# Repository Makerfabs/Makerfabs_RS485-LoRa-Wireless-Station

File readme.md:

# Industrial-grade Soil Remote Monitor

```c++
/*
Version:		V2.0
Author:			Vincent
Create Date:	2023/3/1
Note:
		2023/3/1	V2.0: Use new sensor, change request code.
*/
```

[toc]

# Makerfabs

[Makerfabs home page](https://www.makerfabs.com/)

[Makerfabs Wiki](https://wiki.makerfabs.com/)

# Industrial-grade Soil Remote Monitor

## Intruduce

Product Link ：[Industrial-grade Soil Remote Monitor(Humidity/ Temperature/ PH/ Nitrogen/ Phosphorus/ Potassium)](https://www.makerfabs.com/industrial-grade-soil-remote-monitor.html) 

Wiki Link : [RS485-LoRa Wireless Station](https://wiki.makerfabs.com/Industrial-grade_Soil_Remote_Monitor.html) 

With the development of agricultural modernization and the popularization of precision agriculture, the remote monitoring of soil parameters such as temperature, moisture, PH, and so on, becomes more important.

This Industry-grade soil remote monitor intends for these applications of agriculture, it is mainly composed of 2 parts:

**1. Remote monitor station with RS485:** developed by Makerfabs, it converts the RS485 signal, which is usually used in agricultural field applications, to wireless connections WIFI (if there is) or Lora, or Bluetooth.
**2. Industrial-grade Soil Sensor:** unlike some other maker-level soil sensors that only output analog voltage that reflects the soil status/changes but not the absolute value, this sensor measures the soil parameters such Temperature/Moisture/PH/Nitrogen/ Phosphorus/Potassium.., with calculated true output, so users can get to know the real soil parameters.

## Feature

- ESP32 WROOM module onboard with the WiFi and Bluetooth
- Arduino Compatible: You can play it with Arduino IDE
- Onboard LoRa module (433Mhz or 868Mhz or 915Mhz)
- 0.91inch I2C OLED display
- Sensor part is waterproof, completely sealed
- Measuring range: -40℃~80℃，0~100% moisture
- Measuring accuracy: ±0.5℃，±3% moisture
- Communication distance: Lora: 2km or more; WIFI: No such parameter
- Power by Micro USB, battery, or DC 5V
- 1000mAh battery, charger IC onboard

# Code

## Compiler Options

**If you have any questions，such as how to install the development board, how to download the code, how to install the library. Please refer to :[Makerfabs_FAQ](https://github.com/Makerfabs/Makerfabs_FAQ)**

- Install board : ESP32 .
- Install library : Adafruit GFX library (V1.10.11) , Adafruit SSD1306 library (V2.4.6) and RadioLib library 4.0.6.
- Upload codes, select "ESP32 Dev Module"

## Sensor User Manual

Cable definition:

- Grey cable: DC 5V power supply +
- Black line: Power ground (GND)
- Yellow and green wires: RS485-A;
- Brown cable: RS485-B.

The sensor uses Modbus RTU.

Request Command：**01 04 00 00 00 07 B1 C8**

- 0x01 Sensor address; 
- 0x04 function code; 
- 0x00 0x00 read register start position; 
- 0x00 0x07 Number of registers read; 
- 0xB1 0xC8  Check

Receive Data：**01 04 0E 01 D7 01 07 00 00 00 46 00 0F 00 14 00 32 CC 93**

- 0x01 Sensor address;
- 0x04 function code;
- 0x0E data length;
- 0x01 0xD7 Soil moisture data 01 D7 (hexadecimal) is 47.1%
- 0x01 0x07 Soil Temperature Data 01 07 (hexadecimal) is 26.3 ° C
- 0x00 0x00 blank
- 0x00 0x46 PH data 00 46 (hexadecimal) is 7.0
- 0x00 0x0F Soil Nitrogen data 00 0F (hexadecimal) is 15mg/kg
- 0x00 0x14 Soil Phosphorus data 00 14 (hexadecimal) is 20mg/kg
- 0x00 0x32 Soil potassium data 00 32 (hexadecimal) is 50mg/kg
- 0xCC 0x93 check

| Parameter   | Address | Range       | Sampling Value | Action    |
| ----------- | ------- | ----------- | -------------- | --------- |
| Humidity    | 0000H   | 0~100%      | /10            | Only Read |
| Temperature | 0001H   | -40~80℃     | /10            | Only Read |
| PH          | 0003H   | 4~9         | /10            | Only Read |
| Nitrogen    | 0004H   | 0~1999mg/kg | /1             | Only Read |
| Phosphorus  | 0005H   | 0~1999mg/kg | /1             | Only Read |
| Potassium   | 0006H   | 0~1999mg/kg | /1             | Only Read |

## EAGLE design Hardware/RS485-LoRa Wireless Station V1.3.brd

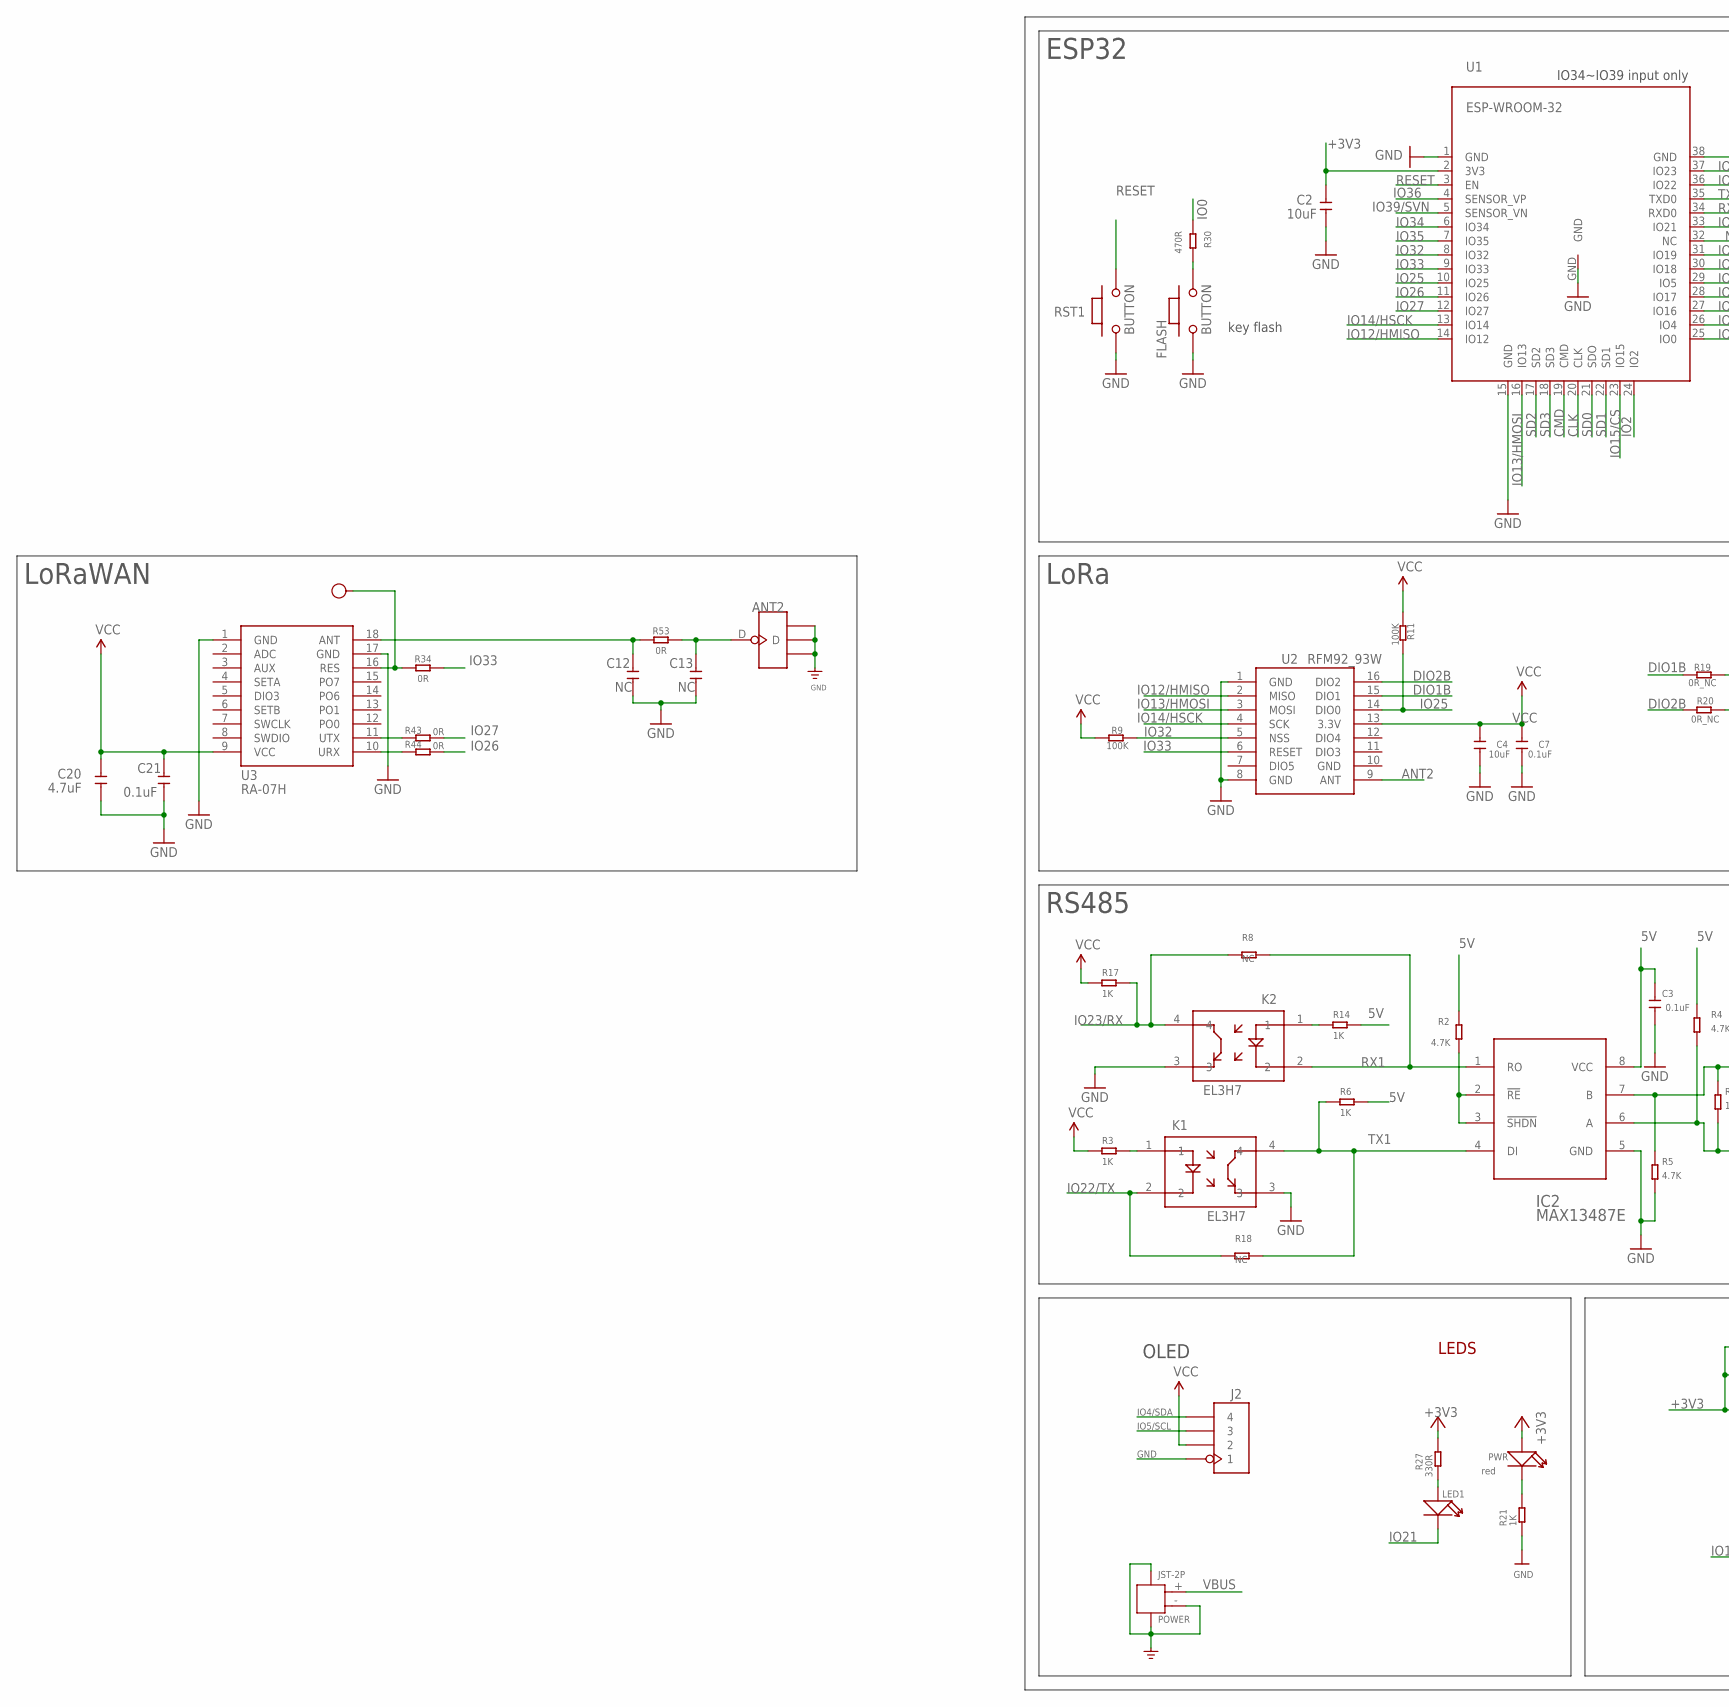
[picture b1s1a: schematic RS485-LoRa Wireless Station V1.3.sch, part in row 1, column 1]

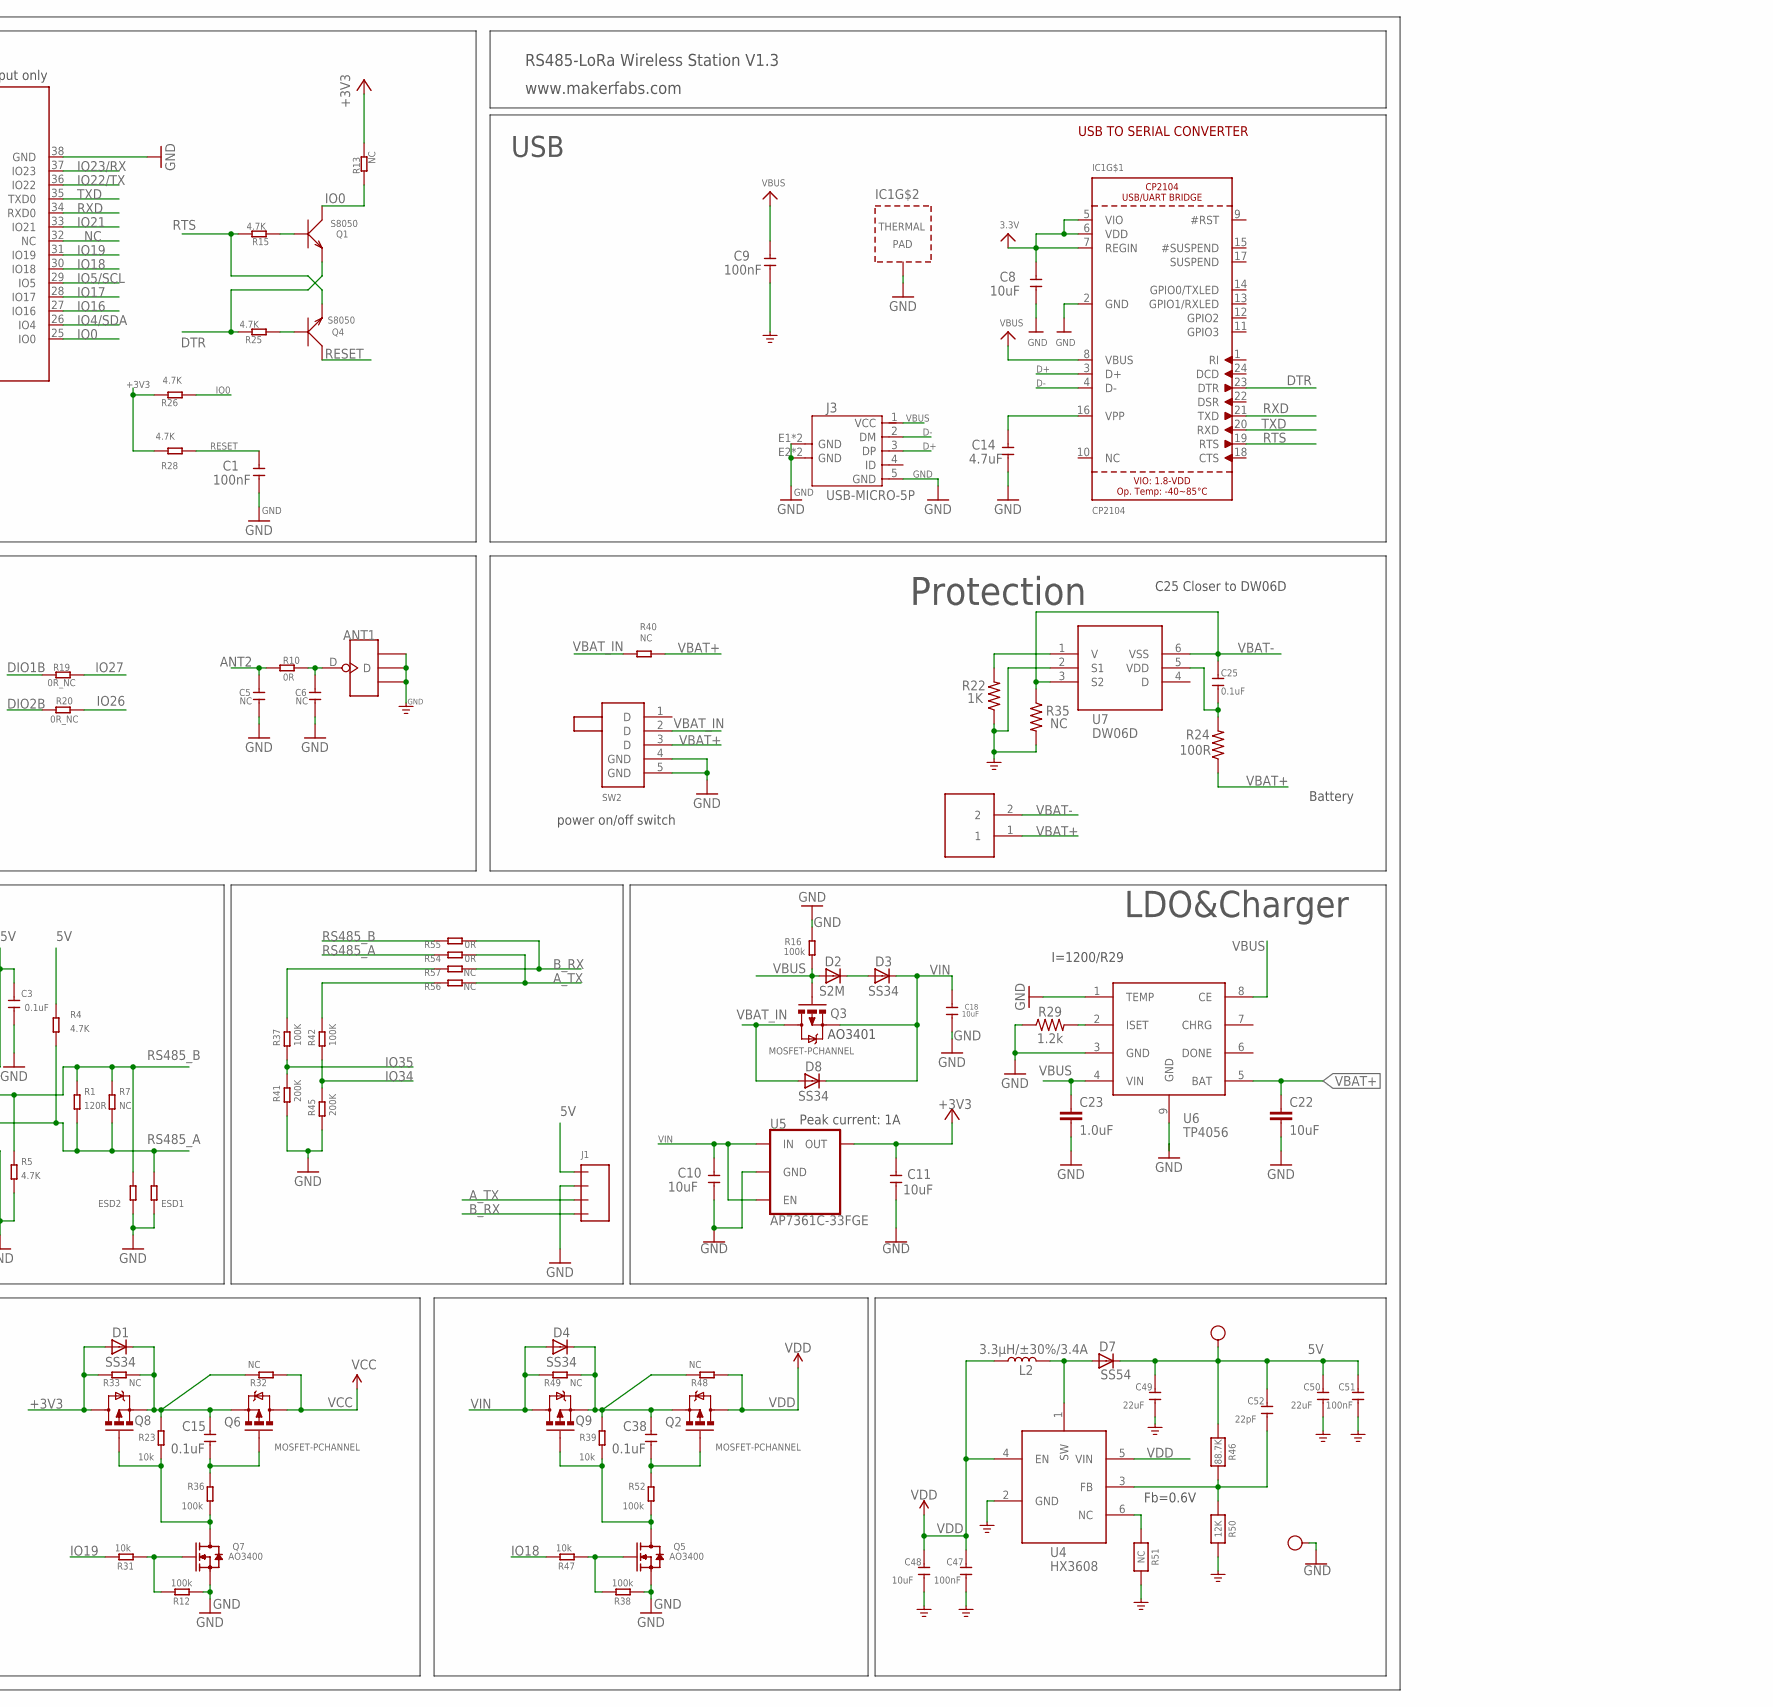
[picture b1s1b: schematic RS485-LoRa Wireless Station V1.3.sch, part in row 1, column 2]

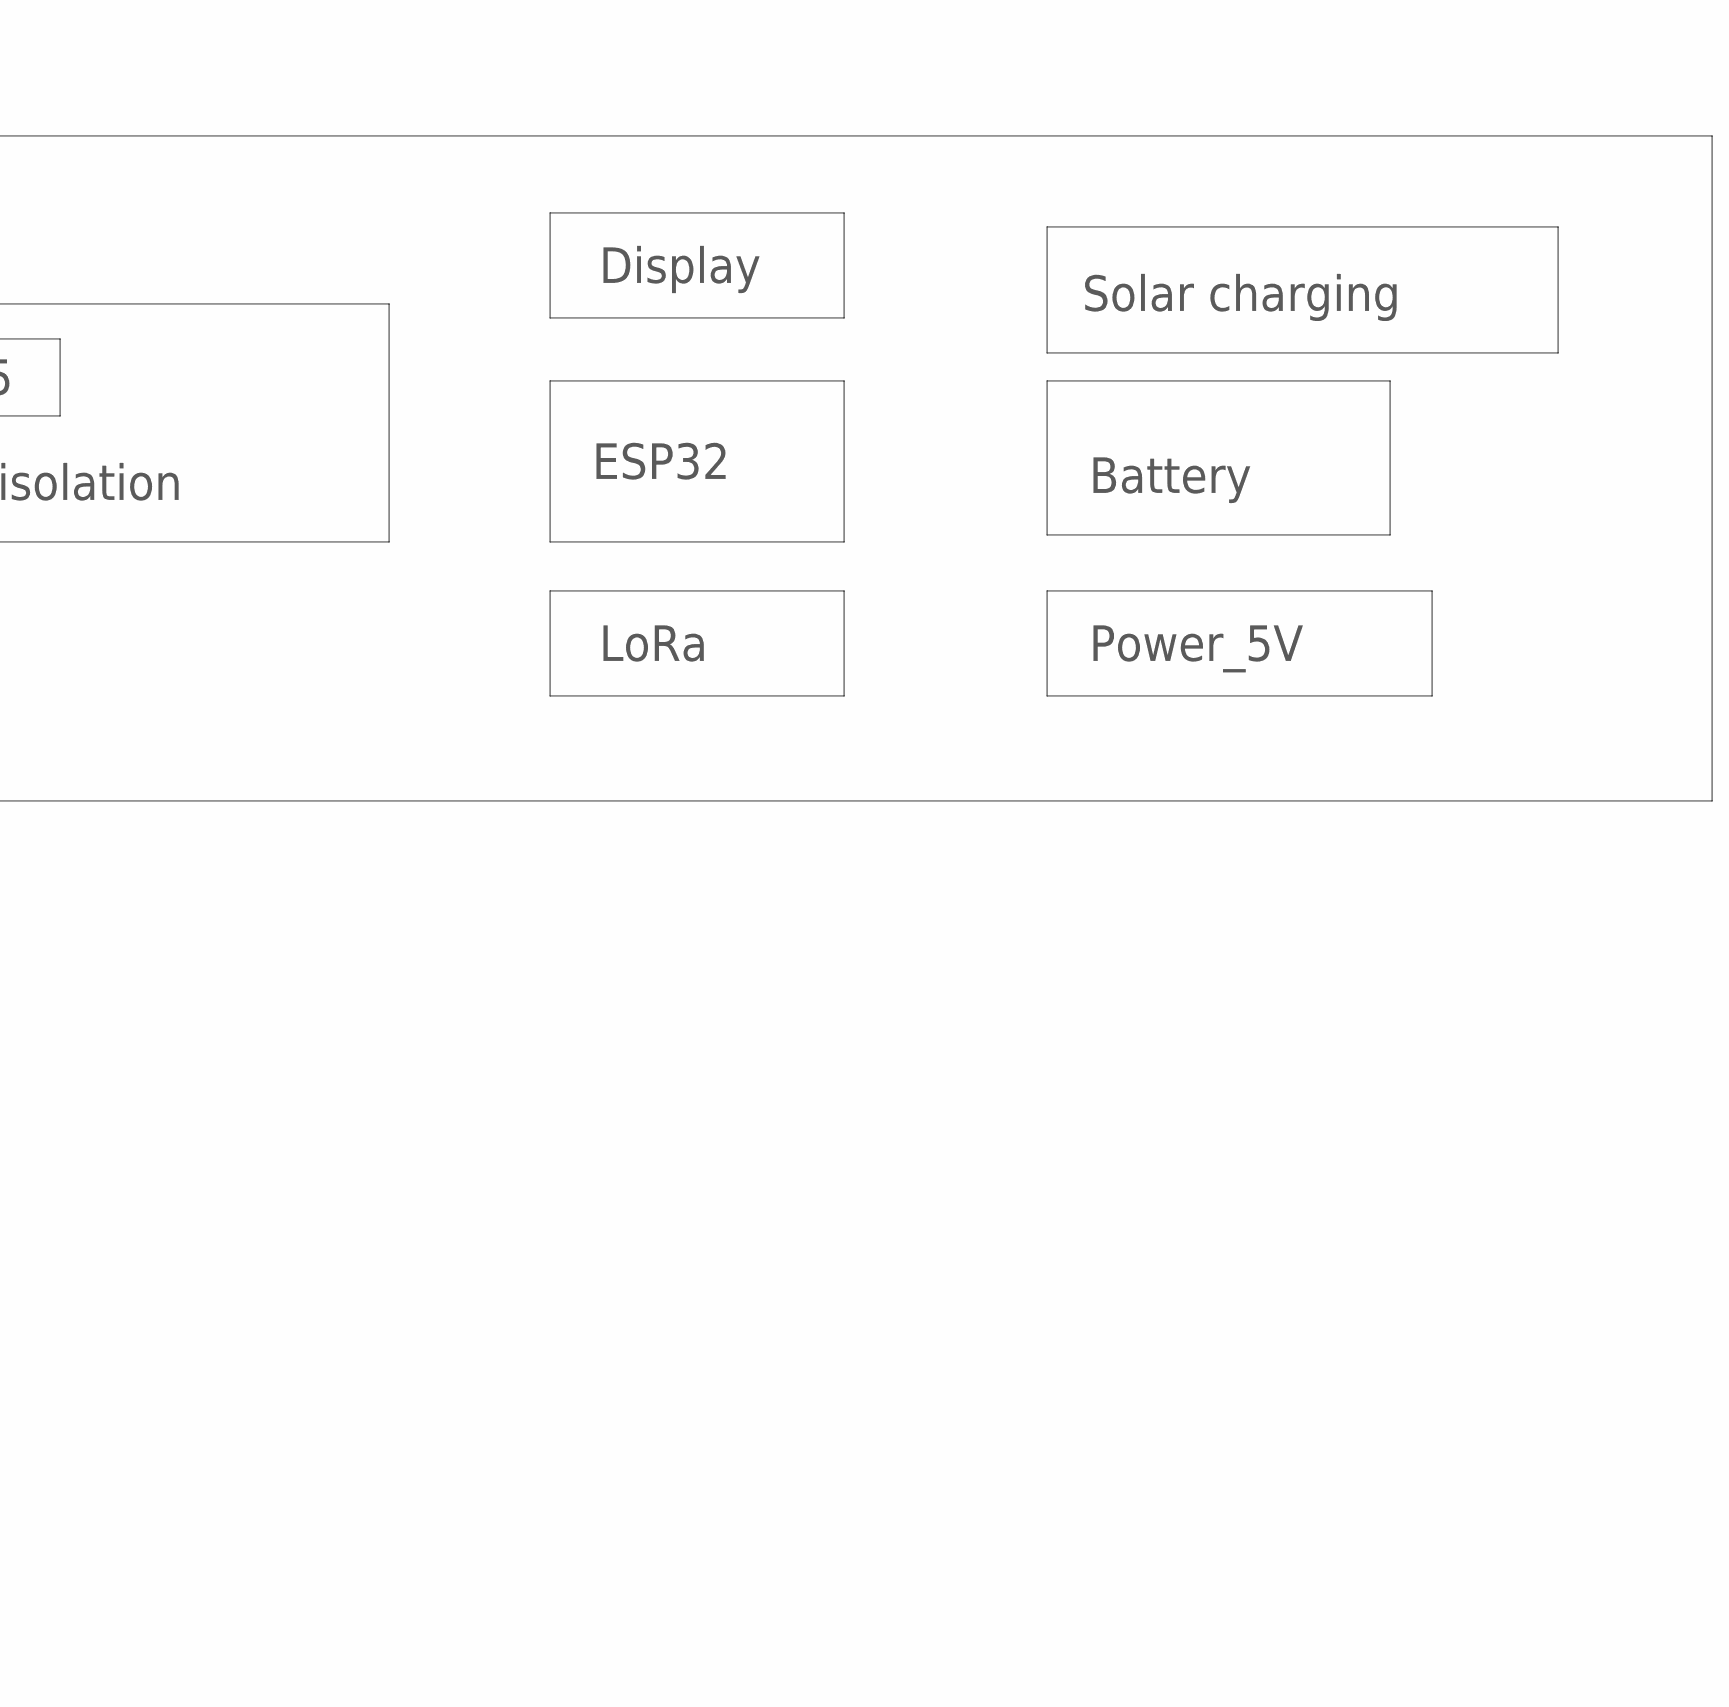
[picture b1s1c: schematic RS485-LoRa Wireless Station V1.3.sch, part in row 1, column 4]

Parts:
5V: TEST-POINT'4545'; TP-D45MIL
ANT1, ANT2: ANTENNA-U-FL; 4P-U-FL
C1, C9, C47, C51: 100nF; C0603
C2, C4, C8, C10, C11, C18, C48: 10uF; C0603
C3, C7, C15, C21, C25, C38: 0.1uF; C0603
C5, C6: NC; DISCRETE_C0603
C12, C13: NC; C0603
C14, C20: 4.7uF; C0603
C22: 10uF; 1206
C23: 1.0uF; 0603
C49, C50: 22uF; C0603
C52: 22pF; C0603
D1, D3, D4, D8: SS34; DO-214AC
D2: S2M; DO-214AC
D7: SS54; DO-214AC
ESD1, ESD2: R-0603; R0603
FLASH: BUTTON; 157SW
GND: TEST-POINT'4545'; TP-D45MIL
IC1: CP2104; QFN24_4MM_SMSC
IC2: MAX13487E; DIP8_MAX13487
J1: J_4P_5.08; DIP4_5.08
J2: HEADER-1X4P; SMD4-2.54P
J3: USB-MICRO-5P; MICRO-USB-5P
J5: PH2.0-2P-90-DIP
K1, K2: EL3H7; SOP-4_P1.27
L2: 3.3µH/±30%/3.4A; CR54
LED1: DISCRETE_LED0603; DISCRETE_LED-0603
POWER: JST-2P; HW2-SMD-2.0-90D
PWR: red; LED-0603
Q1, Q4: S8050; SOT23
Q2, Q3, Q6, Q8, Q9: MOSFET-PCHANNEL; SOT23-3
Q5, Q7: AO3400; SOT23@1
R1: 120R; R0603
R2, R4, R5, R15, R25, R26, R28: 4.7K; R0603
R3, R6, R14, R17, R21: 1K; R0603
R7, R8, R13, R18, R32, R33, R40, R48, R49, R56, R57: NC; R0603
R9, R11, R37, R42: 100K; R0603
R10: 0R; DISCRETE_R0603
R12, R16, R36, R38, R52: 100k; R0603
R19, R20: 0R_NC; R0603
R22: 1K; 0603
R23, R31, R39, R47: 10k; R0603
R24: 100R; 0603
R27: 330R; R0603
R29: 1.2k; 0603
R30: 470R; R0603
R34, R43, R44, R53, R54, R55: 0R; R0603
R35: NC; 0603
R41, R45: 200K; R0603
R46: 88.7K; 0603-NO
R50: 12K; 0603-NO
R51: NC; 0603-NO
RES: TEST-POINT'4545'; TP-D45MIL; PARTNO DNP
RST1: BUTTON; 157SW
SW2: SWITCH; DIP5-8.6*4.5MM
U1: ESP-WROOM-32
U2: RFM92_93W
U3: RA-07H; SMD18-127P-1600L1600W
U4: HX3608; SOT-23-6
U5: AP7361C-33FGE; 8-UDFN
U6: TP4056; SOP8-1.27P
U7: DW06D; SOT-23-6

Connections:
5V: 5V.T, C3.2, C49.1, C50.1, C51.1, C52.1, D7.C, IC2.8 (VCC), J1.P$1 (1), R2.2, R4.2, R6.1, R14.1, R46.1
+3V3: C2.2, C8.2, C11.2, D1.A, IC1.5 (VIO), IC1.6 (VDD), IC1.7 (REGIN), PWR.+, Q8.3 (D), R13.1, R26.1, R27.2, R28.1, R33.2, U1.2 (3V3), U5.1 (OUT)
ANT2: C5.2, R10.1, U2.9 (ANT)
A_TX: J1.P$3 (3), R54.1, R56.1
B_RX: J1.P$4 (4), R55.1, R57.1
CLK: U1.20 (CLK)
CMD: U1.19 (CMD)
D+: IC1.3 (D+), J3.3 (DP)
D-: IC1.4 (D-), J3.2 (DM)
DIO1B: R19.2, U2.15 (DIO1)
DIO2B: R20.2, U2.16 (DIO2)
DTR: IC1.23 (DTR), Q1.2 (E), R25.1
GND: ANT1.GND1, ANT1.GND2, ANT1.GND3, ANT2.GND1, ANT2.GND2, ANT2.GND3, C1.1, C2.1, C3.1, C4.1, C5.1, C6.1, C7.1, C8.1, C9.1, C10.1, C11.1, C12.1, C13.1, C14.1, C18.1, C20.1, C21.1, C22.2, C23.2, C47.2, C48.2, C49.2, C50.2, C51.2, ESD1.1, ESD2.1, FLASH.1, GND.T, IC1.2 (GND), IC1.THERM (TP), IC2.5 (GND), J1.P$2 (2), J2.1, J3.5 (GND), J3.E1 (GND), J3.E2 (GND), J3.P1 (GND), J3.P2 (GND), K1.3, K2.3, POWER.3, POWER.4, POWER.- (2), Q5.2 (S), Q7.2 (S), R5.1, R12.1, R16.2, R21.1, R22.1, R29.1, R35.2, R38.1, R41.2, R45.2, R50.2, R51.2, RST1.1, SW2.4 (GND), SW2.5 (GND), U1.1 (GND), U1.15 (GND), U1.38 (GND), U1.GND, U2.1 (GND), U2.8 (GND), U2.10 (GND), U3.1 (GND), U3.17 (GND), U4.2 (GND), U5.4 (GND), U5.EP (GND), U6.1 (TEMP), U6.3 (GND), U6.9 (GND), U7.2 (S1)
IO0: Q1.3 (C), R13.2, R26.2, R30.2, U1.25 (IO0)
IO2: U1.24 (IO2)
IO4/SDA: J2.4, U1.26 (IO4)
IO5/SCL: J2.3, U1.29 (IO5)
IO12/HMISO: U1.14 (IO12), U2.2 (MISO)
IO13/HMOSI: U1.16 (IO13), U2.3 (MOSI)
IO14/HSCK: U1.13 (IO14), U2.4 (SCK)
IO15/CS: U1.23 (IO15)
IO16: U1.27 (IO16)
IO17: U1.28 (IO17)
IO18: R47.2, U1.30 (IO18)
IO19: R31.2, U1.31 (IO19)
IO21: LED1.-, U1.33 (IO21)
IO22/TX: K1.2, R18.2, U1.36 (IO22)
IO23/RX: K2.4, R8.2, R17.1, U1.37 (IO23)
IO25: R11.1, U1.10 (IO25), U2.14 (DIO0)
IO26: R20.1, R44.2, U1.11 (IO26)
IO27: R19.1, R43.2, U1.12 (IO27)
IO32: R9.1, U1.8 (IO32), U2.5 (NSS)
IO33: R34.2, U1.9 (IO33), U2.6 (RESET)
IO34: R42.2, R45.1, U1.6 (IO34)
IO35: R37.2, R41.1, U1.7 (IO35)
IO36: U1.4 (SENSOR_VP)
IO39/SVN: U1.5 (SENSOR_VN)
ISET: R29.2, U6.2 (ISET)
unnamed: K2.1, R14.2
unnamed: D2.C, D3.A
unnamed: K1.1, R3.1
unnamed: ANT1.D, C6.2, R10.2
unnamed: LED1.+, R27.1
unnamed: C14.2, IC1.16 (VPP)
unnamed: PWR.-, R21.2
unnamed: Q4.1 (B), R25.2
unnamed: Q1.1 (B), R15.2
unnamed: FLASH.2, R30.1
unnamed: C38.1, Q2.1 (G), R52.2
unnamed: Q5.1 (G), R38.2, R47.1
unnamed: C15.1, Q6.1 (G), R36.2
unnamed: Q7.1 (G), R12.2, R31.1
unnamed: C15.2, D1.C, Q6.2 (S), Q8.2 (S), R23.2, R32.2, R33.1
unnamed: C25.2, R24.2, U7.5 (VDD)
unnamed: R22.2, U7.1 (V)
unnamed: Q7.3 (D), Q8.1 (G), R23.1, R36.1
unnamed: R42.1, R56.2
unnamed: C38.2, D4.C, Q2.2 (S), Q9.2 (S), R39.2, R48.2, R49.1
unnamed: R37.1, R57.2
unnamed: R43.1, U3.11 (UTX)
unnamed: D7.A, L2.P$2 (2), U4.1 (SW)
unnamed: R44.1, U3.10 (URX)
unnamed: C52.2, R46.2, R50.1, U4.3 (FB)
unnamed: R51.1, U4.6 (NC)
unnamed: R34.1, RES.T, U3.16 (RES)
unnamed: C12.2, R53.1, U3.18 (ANT)
unnamed: ANT2.D, C13.2, R53.2
unnamed: Q5.3 (D), Q9.1 (G), R39.1, R52.1
unnamed: IC2.2 (!RE), IC2.3 (!SHDN), R2.1
NC: U1.32 (NC)
RESET: C1.2, Q4.3 (C), R28.2, RST1.2, U1.3 (EN)
RS485_A: ESD1.2, IC2.6 (A), R1.1, R4.1, R7.1, R54.2
RS485_B: ESD2.2, IC2.7 (B), R1.2, R5.2, R7.2, R55.2
RTS: IC1.19 (RTS), Q4.2 (E), R15.1
RX1: IC2.1 (RO), K2.2, R8.1
RXD: IC1.21 (TXD), U1.34 (RXD0)
SD0: U1.21 (SDO)
SD1: U1.22 (SD1)
SD2: U1.17 (SD2)
SD3: U1.18 (SD3)
TX1: IC2.4 (DI), K1.4, R6.2, R18.1
TXD: IC1.20 (RXD), U1.35 (TXD0)
VBAT+: C22.1, J5.1, R24.1, R40.2, SW2.3 (D), U6.5 (BAT)
VBAT-: C25.1, J5.2, R35.1, U7.3 (S2), U7.6 (VSS)
VBAT_IN: D8.A, Q3.3 (D), R40.1, SW2.2 (D)
VBUS: C9.2, C23.1, D2.A, IC1.8 (VBUS), J3.1 (VCC), POWER.+ (1), Q3.1 (G), R16.1, U6.4 (VIN), U6.8 (CE)
VCC: C4.2, C7.2, C20.2, C21.2, J2.2, Q6.3 (D), R3.2, R9.2, R11.2, R17.2, R32.1, U2.13 (3.3V), U3.9 (VCC)
VDD: C47.1, C48.1, L2.P$1 (1), Q2.3 (D), R48.1, U4.4 (EN), U4.5 (VIN)
VIN: C10.2, C18.2, D3.C, D4.A, D8.C, Q3.2 (S), Q9.3 (D), R49.2, U5.5 (EN), U5.8 (IN)

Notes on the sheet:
Peak current: 1A
LDO&Charger
AO3401
I=1200/R29
Battery
C25 Closer to DW06D
Protection
power on/off switch
OLED
Fb=0.6V
ESP32
LoRa
Power_5V
Solar charging
RS485
LEDS
IO34~IO39 input only
key flash
Photoelectric isolation
USB TO SERIAL CONVERTER
Display
USB
LoRaWAN
RS485-LoRa Wireless Station V1.3
www.makerfabs.com

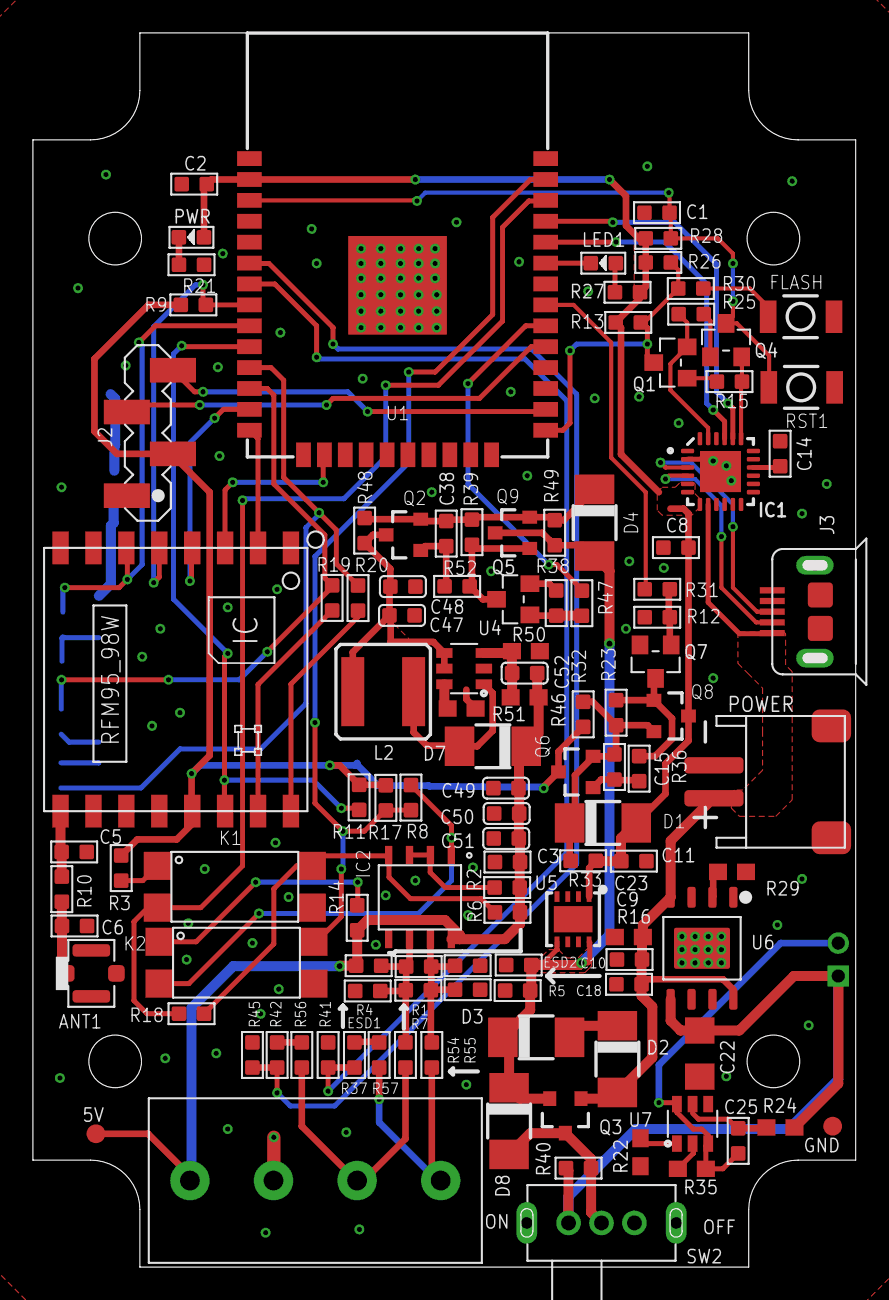
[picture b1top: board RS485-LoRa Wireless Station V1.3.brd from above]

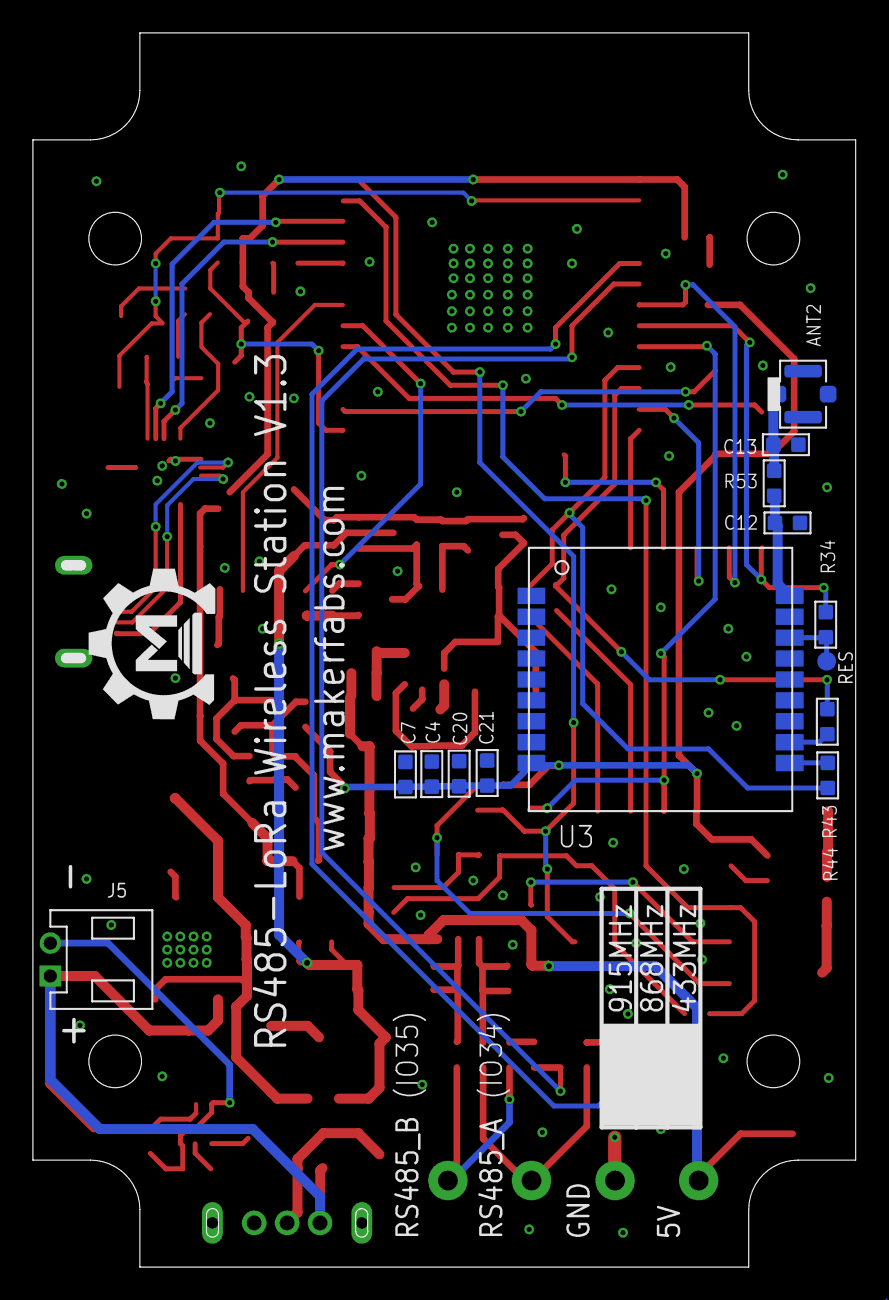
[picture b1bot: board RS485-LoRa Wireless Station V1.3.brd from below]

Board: 2 copper layers, 50.0 x 75.0 mm, 130 parts (15 on the bottom side), 76 nets.

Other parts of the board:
U$9: MAKERFABS_0.3

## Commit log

2021-09-13 Create hardware and demo code
2021-09-16 create LoRa receiver
2021-10-23 create display-NPK
2023-03-01 New sensor update
2023-05-24 Compatible with two sensors.
2023-05-29 Add sensor test demo

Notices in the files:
parts and their libraries:
microbuilder: This work is placed in the public domain, and may be freely used for commercial and non-commercial work with the following conditions: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
SparkFun-Capacitors: Licensing: Creative Commons ShareAlike 4.0 International - https://creativecommons.org/licenses/by-sa/4.0
